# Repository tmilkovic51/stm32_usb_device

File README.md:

# STM32 USB device
A simple PCB consisting of an STM32F103C8T6 microcontroller acting as a USB device and 3 UART pin headers connected to MCU's UART pins.

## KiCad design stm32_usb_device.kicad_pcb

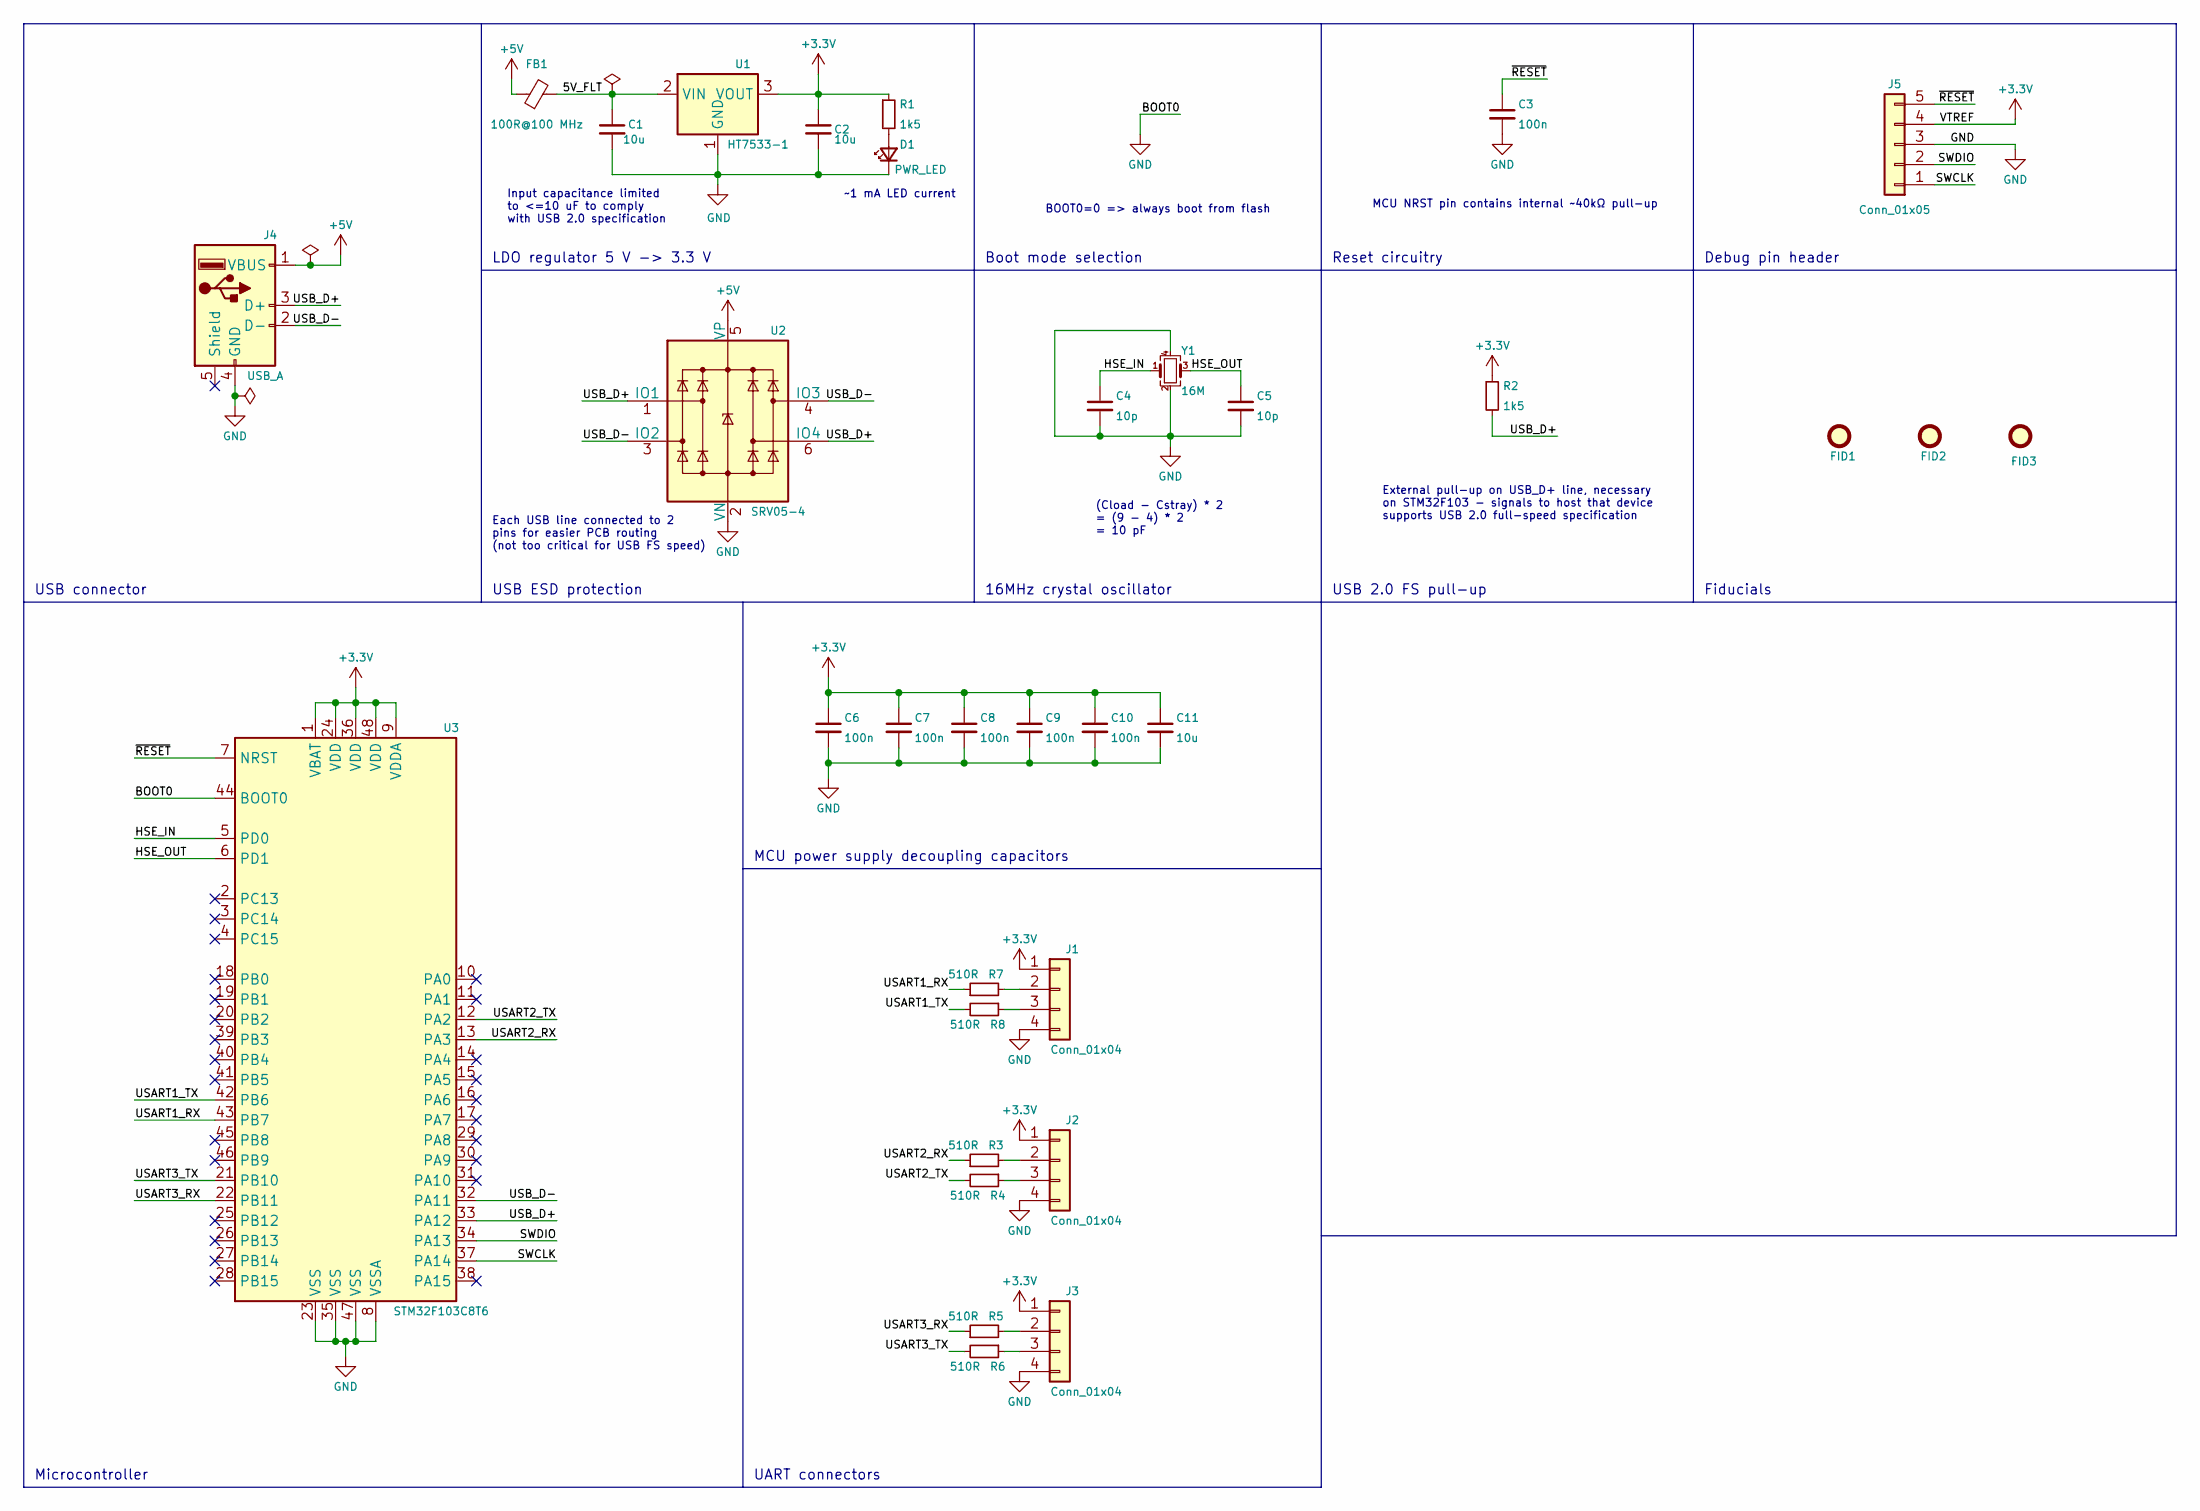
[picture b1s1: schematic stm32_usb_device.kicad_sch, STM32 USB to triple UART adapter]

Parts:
C1, C2, C11: 10u; C_0603_1608Metric; LCSC C96446
C3, C6, C7, C8, C9, C10: 100n; C_0402_1005Metric; LCSC C307331
C4, C5: 10p; C_0402_1005Metric; LCSC C32949
D1: PWR_LED; LED_0603_1608Metric; LCSC C2286
FB1: 100R@100 MHz; L_0805_2012Metric
FID1, FID2, FID3: Fiducial; Fiducial_1mm_Mask2mm
J1, J2, J3: Conn_01x04; PinHeader_1x04_P2.54mm_Vertical
J4: USB_A; USB_A_4pin
J5: Conn_01x05; PinHeader_1x05_P1.27mm_Vertical_SMD_Pin1Left
R1, R2: 1k5; R_0402_1005Metric; LCSC C25867
R3, R4, R5, R6, R7, R8: 510R; R_0402_1005Metric; LCSC C25123
U1: HT7533-1; SOT-89-3; LCSC C14289
U2: SRV05-4; SOT-23-6; LCSC C7420376
U3: STM32F103C8T6; LQFP-48_7x7mm_P0.5mm; LCSC C8734
Y1: 16M; Crystal_SMD_3225-4Pin_3.2x2.5mm; LCSC C13738

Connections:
+3.3V: C2.1, C6.1, C7.1, C8.1, C9.1, C10.1, C11.1, J1.1, J2.1, J3.1, J5.4, R1.1, R2.1, U1.3 (VOUT), U3.1 (VBAT), U3.9 (VDDA), U3.24 (VDD), U3.36 (VDD), U3.48 (VDD)
+5V: FB1.1, J4.1 (VBUS), U2.5 (VP)
/5V_FLT: C1.1, FB1.2, U1.2 (VIN)
/HSE_IN: C4.1, U3.5 (PD0), Y1.1
/HSE_OUT: C5.1, U3.6 (PD1), Y1.3
/SWCLK: J5.1, U3.37 (PA14)
/SWDIO: J5.2, U3.34 (PA13)
/USART1_RX: R7.1, U3.43 (PB7)
/USART1_TX: R8.2, U3.42 (PB6)
/USART2_RX: R3.1, U3.13 (PA3)
/USART2_TX: R4.2, U3.12 (PA2)
/USART3_RX: R5.1, U3.22 (PB11)
/USART3_TX: R6.2, U3.21 (PB10)
/USB_D+: J4.3 (D+), R2.2, U2.1 (IO1), U2.6 (IO4), U3.33 (PA12)
/USB_D-: J4.2 (D-), U2.3 (IO2), U2.4 (IO3), U3.32 (PA11)
/~RESET: C3.1, J5.5, U3.7 (NRST)
GND: C1.2, C2.2, C3.2, C4.2, C5.2, C6.2, C7.2, C8.2, C9.2, C10.2, C11.2, D1.1 (K), J1.4, J2.4, J3.4, J4.4 (GND), J5.3, U1.1 (GND), U2.2 (VN), U3.8 (VSSA), U3.23 (VSS), U3.35 (VSS), U3.44 (BOOT0), U3.47 (VSS), Y1.2, Y1.4
unnamed: D1.2 (A), R1.2
unnamed: J1.2, R7.2
unnamed: J1.3, R8.1
unnamed: J2.2, R3.2
unnamed: J2.3, R4.1
unnamed: J3.2, R5.2
unnamed: J3.3, R6.1

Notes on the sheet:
External pull-up on USB_D+ line, necessary on STM32F103 - signals to host that device supports USB 2.0 full-speed specification
LDO regulator 5 V -> 3.3 V
USB ESD protection
Each USB line connected to 2 pins for easier PCB routing (not too critical for USB FS speed)
Debug pin header
USB connector
BOOT0=0 => always boot from flash
Reset circuitry
Boot mode selection
~1 mA LED current
USB 2.0 FS pull-up
Microcontroller
Fiducials
(Cload - Cstray) * 2 = (9 - 4) * 2 = 10 pF
MCU power supply decoupling capacitors
16MHz crystal oscillator
UART connectors
Input capacitance limited to <=10 uF to comply with USB 2.0 specification
MCU NRST pin contains internal ~40kΩ pull-up

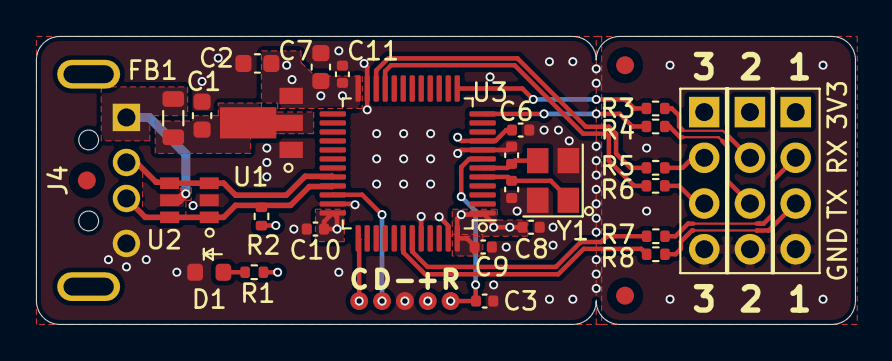
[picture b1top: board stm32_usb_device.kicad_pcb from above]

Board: 4 copper layers, 45.5 x 16.0 mm, 33 parts (0 on the bottom side), 24 nets.

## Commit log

2024-01-02 Initialize KiCAD project
2024-01-02 Add USB connector, protection diodes and MCU
2024-01-02 schematic: Add power supply, decoupling caps, pin headers
2024-01-11 Add USB connector and UART isolators
    Make initial PCB layout and routing
2024-01-17 Finish PCB routing
2024-01-18 Remove unused net labels
2024-09-15 Update project to KiCad v6
2024-09-15 Add image of finished PCBA to doc folder
